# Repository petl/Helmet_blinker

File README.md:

<p><h2> Motivation</h2> </p><br />
Last year I got a new helmet to make cycling for myself a bit safer. The helmet is an ABUS Hyban 2.0 in a stylish color with an integrated LED backlight, which helps others see me at night. Unfortunately the original light is powered by a single CR2032 coin cell, which not only limits its runtime severely, but also is not rechargeable. There even is a <a href='https://www.youtube.com/watch?v=HbjWTI32BtE'>video</a> on how to change the coin cell. This itself is just how ABUS makes products, but what really dumbfounded me were the misaligned LEDs. They just light straight into the rubber part of the light and only some scattered light can be seen from outside. Interestingly enough, the light made it to version 6 as the photo below shows "ACHV_V06". <br><br>
Long story short: I made a rechargeable drop in replacement for the original light. <br><br>

<p>If you're interested in this project, take a look at the <a href='https://quiescentcurrent.com/blog/post.php?p_id=67'>blog</a> or just write a message or leave a comment. If you want to buy one, here's the tindie link: <a href='https://www.tindie.com/products/petl/rechargeable-led-bicycle-helmet-light/'>Rechargeable LED bicycle helmet light</a>   </p>

<p align="right">
<br>The original light on the left, the new one on the right.</p>  <p>

<h2> Schematics </h2> </p>
There probably is a reason why the original light was not rechargeable and it's most certainly money. The most complex part for the PCB was the charging solution around the TP4056 IC. The LiPo is fully protected: over- and undervoltage, temperature limit and short circuit. There is not a lot that can go wrong anymore with the battery which is a reassuring since it is worn near your head. <br><br>
Besides this, the most interesting area is around the ATTiny10 microcontroller. It get programmed via a programming header which I made myself out of some pogo pins. It can detect the push button being pressed and then run some funky blinking on the six red LEDs. <br><br>
<p align="right">
<br>Schematics for v0.2.</p> 

<h2> Hardware </h2> </p>
<p>The hardware assembly was mostly done by jlcpcb (unfortunately not a sponsor). I only had to do the battery and USB connector. The connector itself is a 90° micro USB which snugs in perfectly next to the battery and rubber protector. A great amount of measuring wnet into the correct positioning of the 6 red LEDs bedind the plastic reflector. This worked out surplrisingly well as the can be individually seen in the top photo. </p>

<p align="right">
<br>Backside of the light while charging</p> 

Since there are always at least 5 PCBs assembled, I got to take a nice shot of them. If you want one for yourself, just shoot me a mail, they are v0.1 though. <br><br>
<p align="right">
<br>PCBs to make more lights. </p> 

There are two more LEDs on the PCB, they are charging indicators and are directly switched by the TP4056.

<p align="right">
<br>Charging indicators for the LiPo cell.</p> 

<h2> Software </h2> </p>
<p>Programming an ATTiny10 was more challenging than expected. Although it is an Atmel microcontroller out of the AT* family it behaves quite differently than the ATTiny 84 or 85 for example. It does not feature a real ICSP programming input and can therefore not just be programmed with the Arduino IDE and a library. The programming protocol is called TPI (Tiny Programming Interface) and luckily  <a href='http://www.technoblogy.com/show?1YQY '>technoblogy</a>  already worked that one out, big thanks to them! It only took me almost a week to find their solution and order the recommended "USBasp" programmer, so use this information wisely. After that is is quite straight forward, a lot of low level register magic combined with the incredibly low power deep sleep of the tiny. There are 4 different modes which are cycled through by pressing the button:<br>
 <ul>
  <li>1: 100% on</li>
  <li>2: 50% on, 500ms period</li>
  <li>3: 20% on, 300ms period</li>
  <li>4: 3% on, 1000ms period</li>
</ul> <br>
 </p>
<p align="right">
<br>Screenshow of the code: <a href='https://github.com/petl/Helmet_blinker'>source</a>  .</p> 

<h2> Runtime </h2> </p>
<p>The most important question was the possible runtime of the setup. The <a href='https://www.ebay.at/itm/332602314162'>battery</a> used is a 3.6V 120mAh LiPo which drives the 6 LEDs at ~10mA each, the ATTiny draws 0.2mA while running. This means that in mode 1 it can do roughly 2h on a single charge. In mode 4, this runtime goes up to 65h, since it is only pulsing the LEDs. <br><br>
Standby time can be calculated with the deep sleep current of the ATTiny of <0.1µA. This would result in 1.5 million hours standy time.. More realistically the rest of the circuit uses more current and limits this time. It still is an impressive number and will definitely be the clickbait in case I make a video about this.  
</p>

<h2> Conclusion </h2> </p>
So that's that, I hope this guide didn't get too long. All the files are on the <a href='https://quiescentcurrent.com/blog/post.php?p_id=67'>blog</a> so you can download them and browse through. I did contact ABUS Germany about my design and the idea to make their products rechargeable, but they never answered. If you have any questions or feedback just write a message or leave a comment <3            <br /><br />

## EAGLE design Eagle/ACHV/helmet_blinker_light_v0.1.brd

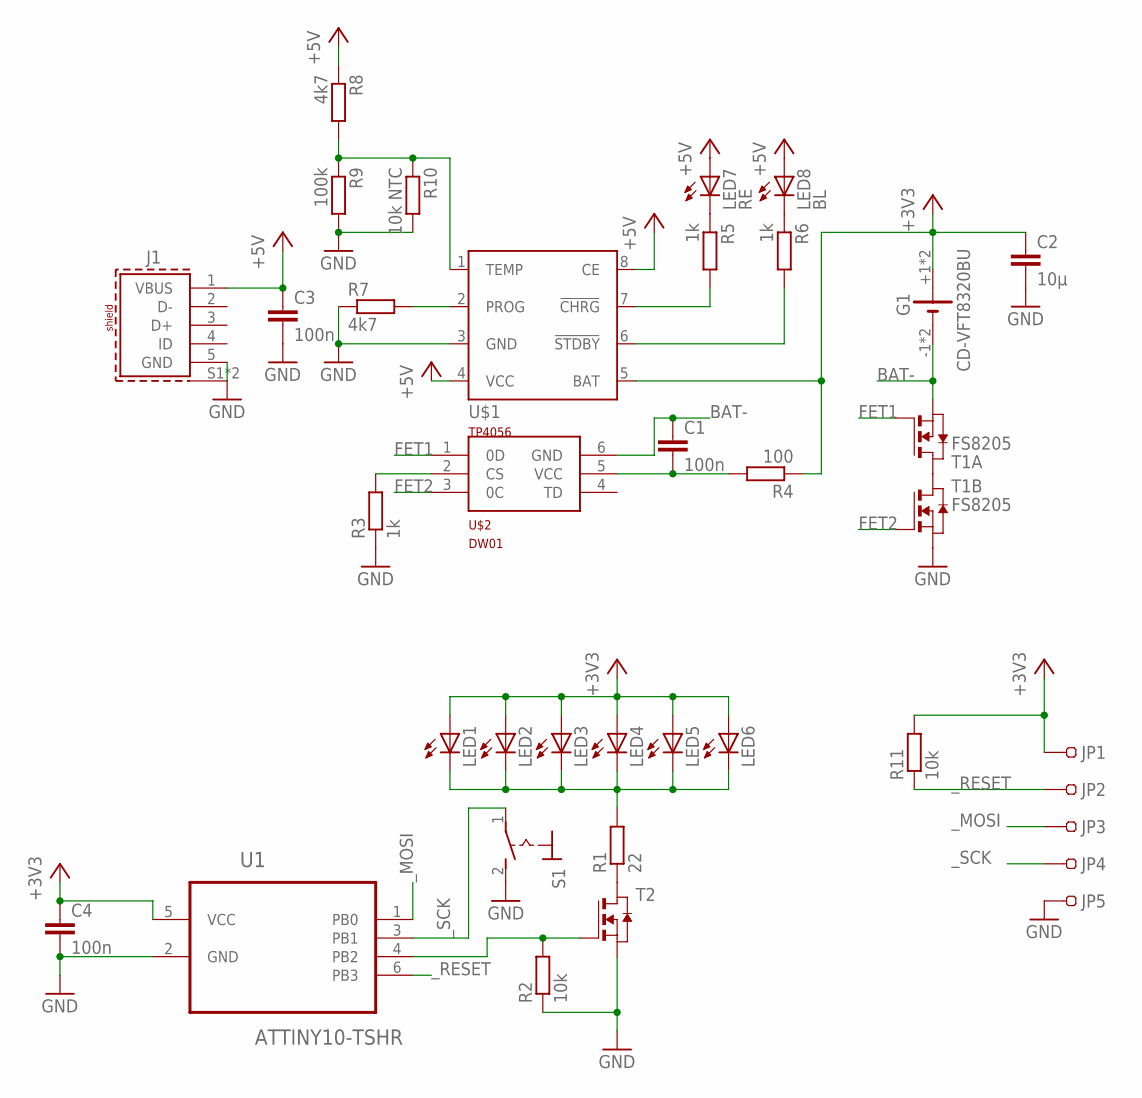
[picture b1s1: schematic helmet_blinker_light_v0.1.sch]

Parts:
C1, C3, C4: 100n; C0402K
C2: 10µ; C0805K
G1: CD-VFT8320BU; CS-VFT8320BU
J1: 614105150621
JP1, JP2, JP3, JP4, JP5: 0.7MM_POGO-PINS
LED1, LED2, LED3, LED4, LED5, LED6: LEDCHIPLED_0805; CHIPLED_0805
LED7: RE; CHIPLED_0805
LED8: BL; CHIPLED_0805
R1: 22; R0805
R2, R11: 10k; R0402
R3, R5, R6: 1k; R0402
R4: 100; R0402
R7, R8: 4k7; R0402
R9: 100k; R0402
R10: 10k NTC; R0805
S1: TS-1088
T1: FS8205; TSSOP-8
T2: NMOSSOT23; SOT-23
U1: ATTINY10-TSHR; SOT95P280X145-6N
U$1: TP4056; SOT23-8
U$2: DW01; SOT23-6

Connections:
+3V3: C2.1, C4.1, G1.+1 (+), G1.+2 (+), JP1.1, LED1.A, LED2.A, LED3.A, LED4.A, LED5.A, LED6.A, R4.1, R11.2, U1.5 (VCC), U$1.5 (BAT)
+5V: C3.1, J1.1 (VBUS), LED7.A, LED8.A, R8.1, U$1.4 (VCC), U$1.8 (CE)
BAT-: C1.1, G1.-1 (-), G1.-2 (-), T1.2 (S), T1.3 (S), U$2.6 (GND)
FET1: T1.4 (G), U$2.1 (0D)
FET2: T1.5 (G), U$2.3 (0C)
GND: C2.2, C3.2, C4.2, J1.5 (GND), J1.S1 (SHIELD), J1.S2 (SHIELD), JP5.1, R2.1, R3.1, R7.1, R9.2, R10.2, S1.2 (S), T1.6 (S), T1.7 (S), T2.2 (S), U1.2 (GND), U$1.3 (GND)
unnamed: T1.1 (D), T1.8 (D)
unnamed: R1.1, T2.1 (D)
unnamed: R3.2, U$2.2 (CS)
unnamed: R2.2, T2.3 (G), U1.4 (PB2)
unnamed: LED1.C, LED2.C, LED3.C, LED4.C, LED5.C, LED6.C, R1.2
unnamed: C1.2, R4.2, U$2.5 (VCC)
unnamed: R7.2, U$1.2 (PROG)
unnamed: R6.2, U$1.6 (!STDBY)
unnamed: LED7.C, R5.1
unnamed: LED8.C, R6.1
unnamed: R5.2, U$1.7 (!CHRG)
unnamed: R8.2, R9.1, R10.1, U$1.1 (TEMP)
_MOSI: JP3.1, U1.1 (PB0)
_RESET: JP2.1, R11.1, U1.6 (PB3)
_SCK: JP4.1, S1.1, U1.3 (PB1)

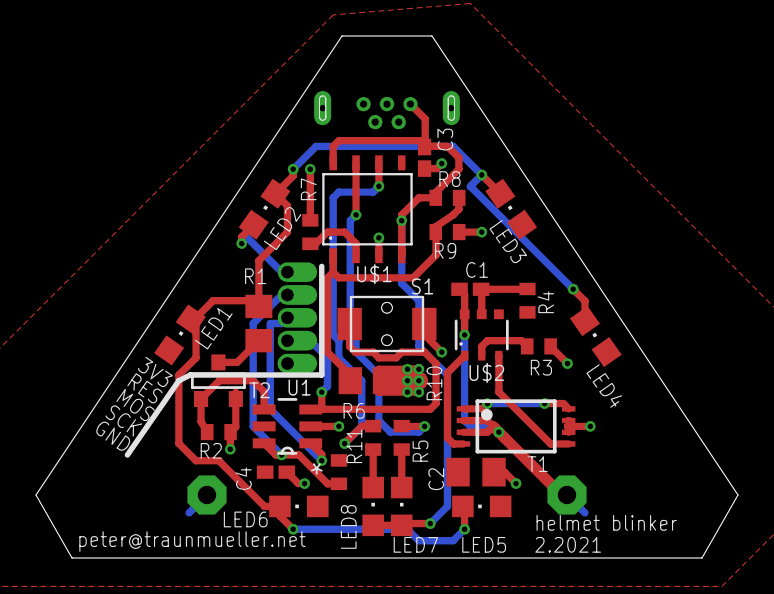
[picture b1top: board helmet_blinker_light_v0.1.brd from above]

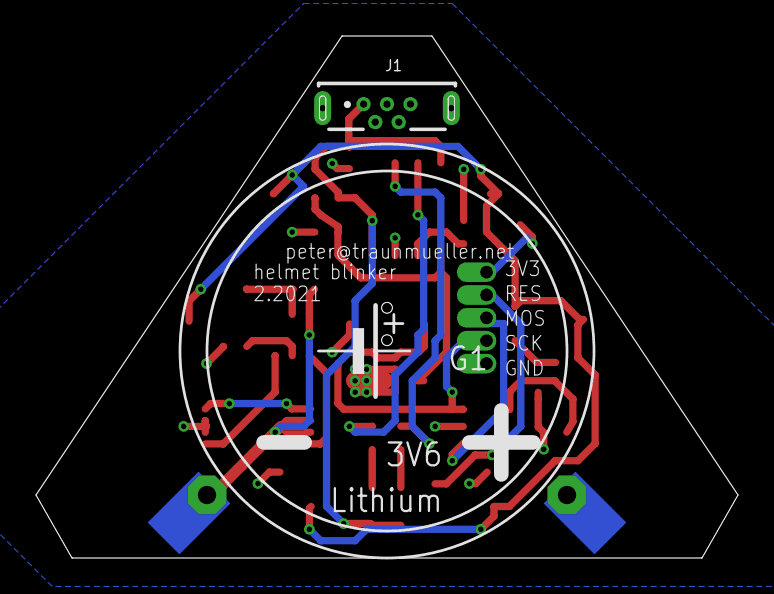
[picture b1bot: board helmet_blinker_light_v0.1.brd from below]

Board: 2 copper layers, 39.0 x 29.0 mm, 36 parts (2 on the bottom side), 21 nets.

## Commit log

2021-08-07 published to github
2021-08-07 added some images
2021-08-07 fixed image links
2021-08-20 added PnP files
2021-08-24 added photo of final thing to readme
2021-09-17 split ACHV and ACY models
2021-09-17 reordered files for ACY vs ACHV models

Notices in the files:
parts and their libraries:
632723300011_Eagle_WR-USB_rev20a: Copyright: Würth Elektronik
